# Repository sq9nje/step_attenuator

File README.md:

# Weinschel Step Attenuator Controller

## Links
- [WT32-ETH01](https://github.com/egnor/wt32-eth01)

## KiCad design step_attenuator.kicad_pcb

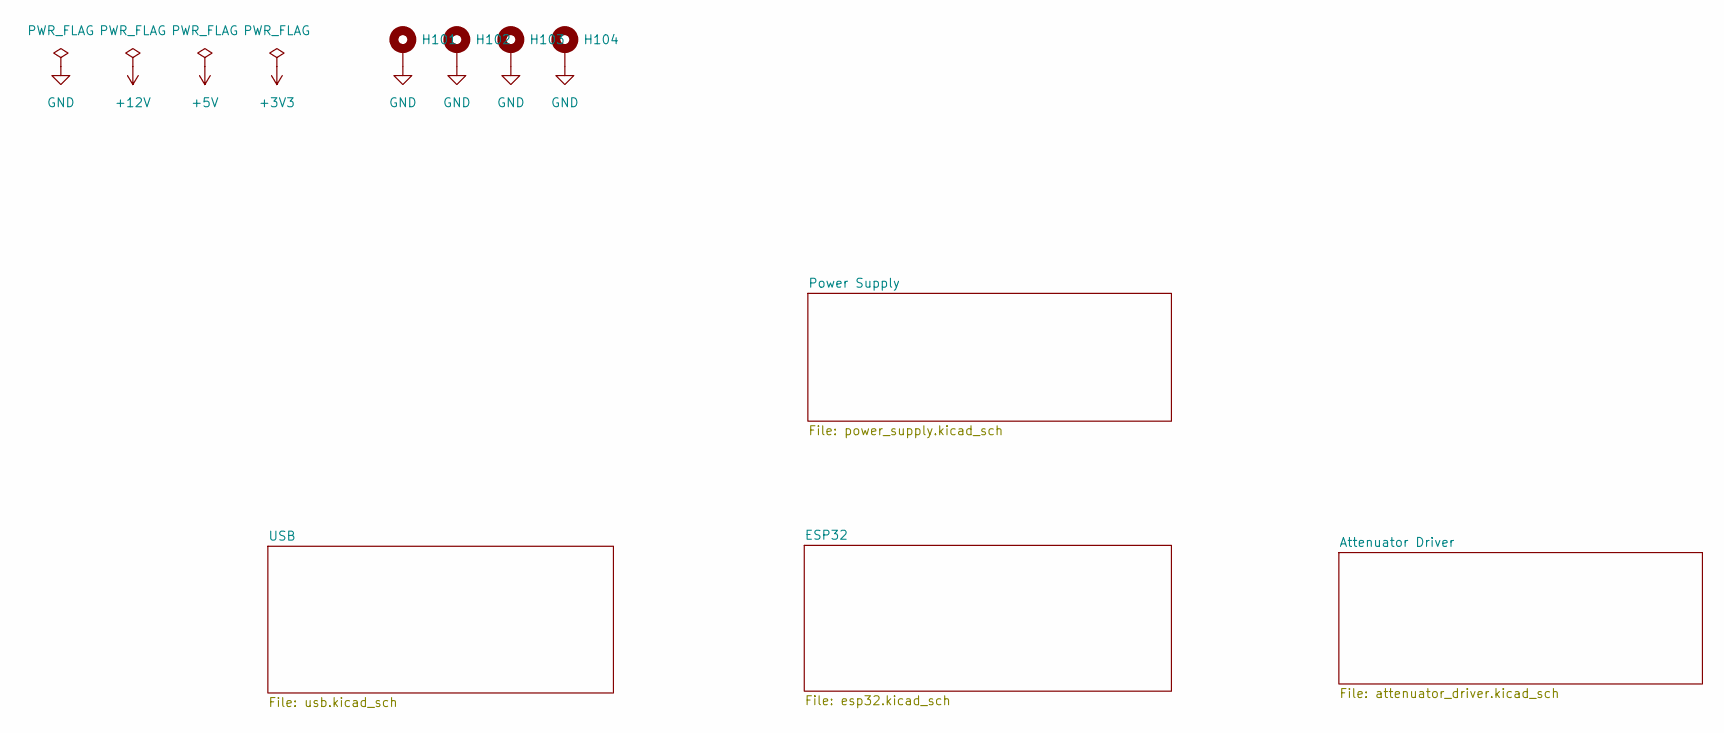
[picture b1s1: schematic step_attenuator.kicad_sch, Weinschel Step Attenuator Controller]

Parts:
H101, H102, H103, H104: MountingHole_Pad; MountingHole_3.2mm_M3_Pad_Via

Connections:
GND: H101.1, H102.1, H103.1, H104.1; also elsewhere on the board

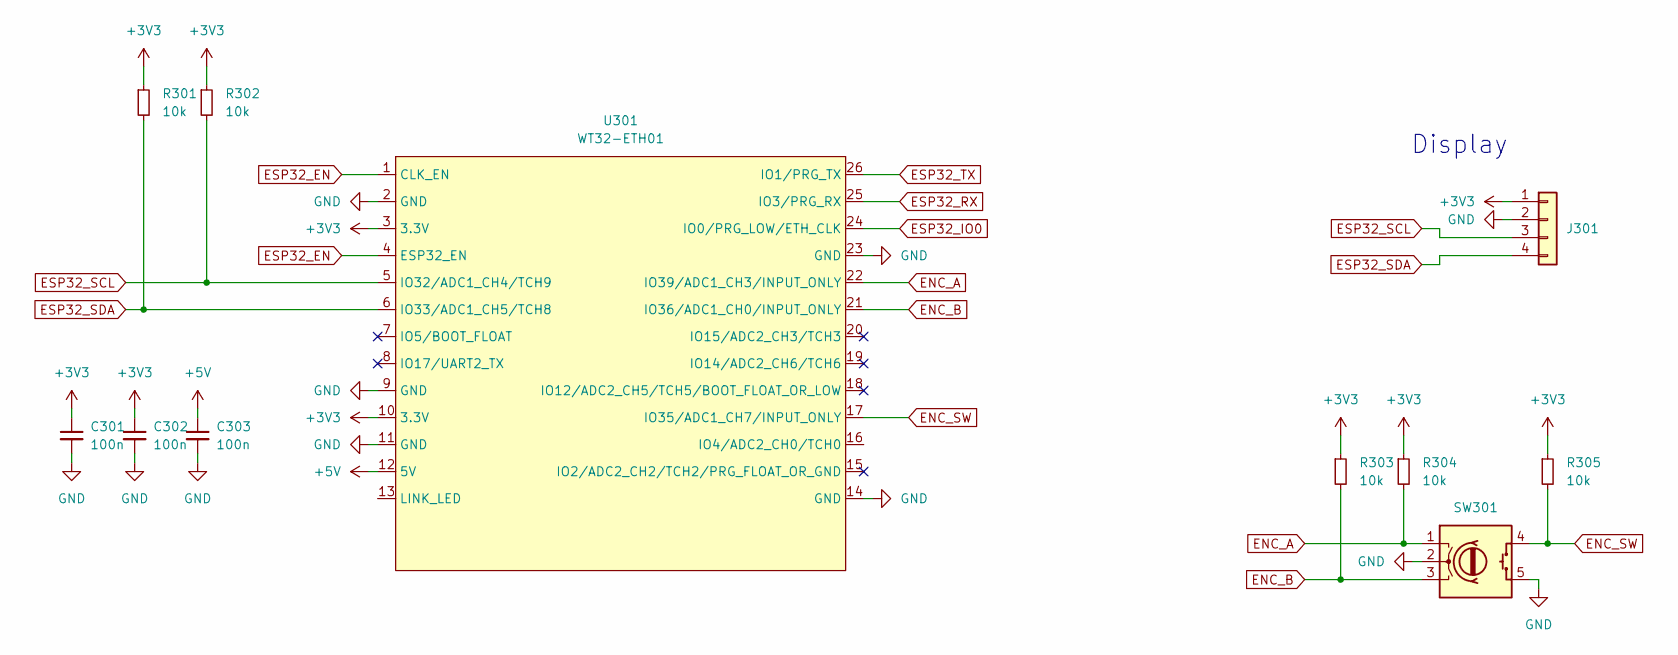
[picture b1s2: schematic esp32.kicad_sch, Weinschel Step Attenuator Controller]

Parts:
C301, C302, C303: 100n; C_0603_1608Metric_Pad1.08x0.95mm_HandSolder
J301: Conn_01x04; JST_XH_B4B-XH-A_1x04_P2.50mm_Vertical
R301, R302, R303, R304, R305: 10k; R_0603_1608Metric_Pad0.98x0.95mm_HandSolder
SW301: RotaryEncoder_Switch; JST_XH_B5B-XH-A_1x05_P2.50mm_Vertical
U301: WT32-ETH01

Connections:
+3V3: C301.1, C302.1, J301.1, R301.1, R302.1, R303.1, R304.1, R305.1, U301.3 (3.3V), U301.10 (3.3V); also elsewhere on the board
+5V: C303.1, U301.12 (5V); also elsewhere on the board
ENC_A: R304.2, SW301.1 (A), U301.22 (IO39/ADC1_CH3/INPUT_ONLY)
ENC_B: R303.2, SW301.3 (B), U301.21 (IO36/ADC1_CH0/INPUT_ONLY)
ENC_SW: R305.2, SW301.4 (S1), U301.17 (IO35/ADC1_CH7/INPUT_ONLY)
ESP32_EN: U301.1 (CLK_EN), U301.4 (ESP32_EN); also elsewhere on the board
ESP32_IO0: U301.24 (IO0/PRG_LOW/ETH_CLK); also elsewhere on the board
ESP32_RX: U301.25 (IO3/PRG_RX); also elsewhere on the board
ESP32_SCL: J301.3, R302.2, U301.5 (IO32/ADC1_CH4/TCH9); also elsewhere on the board
ESP32_SDA: J301.4, R301.2, U301.6 (IO33/ADC1_CH5/TCH8); also elsewhere on the board
ESP32_TX: U301.26 (IO1/PRG_TX); also elsewhere on the board
GND: C301.2, C302.2, C303.2, J301.2, SW301.2 (C), SW301.5 (S2), U301.2 (GND), U301.9 (GND), U301.11 (GND), U301.14 (GND), U301.23 (GND); also elsewhere on the board

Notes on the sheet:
Display

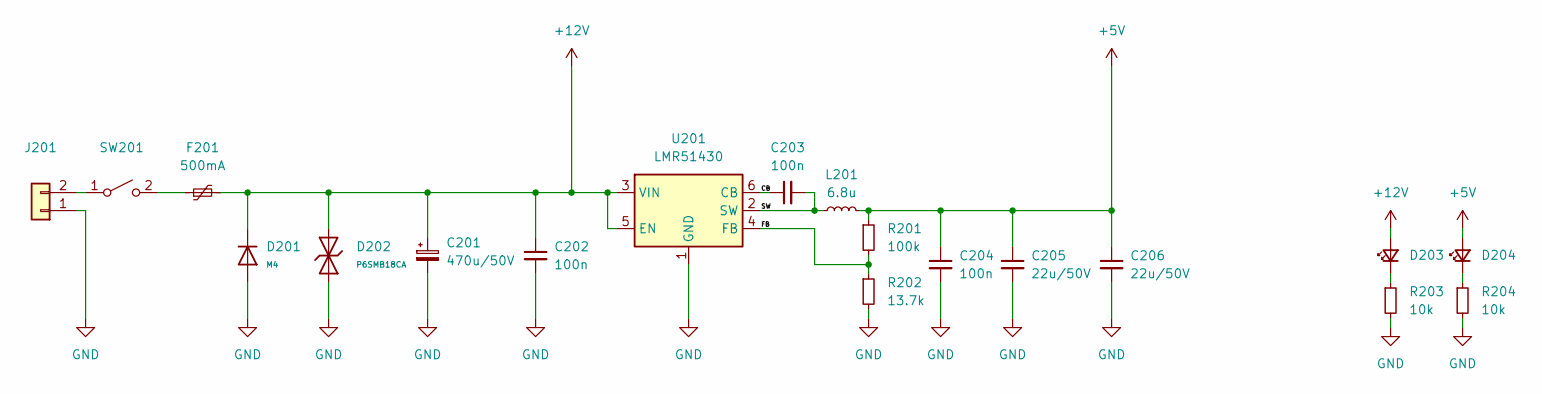
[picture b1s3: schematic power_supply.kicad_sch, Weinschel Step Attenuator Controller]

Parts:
C201: 470u/50V; CP_Radial_D10.0mm_P5.00mm
C202, C203, C204: 100n; C_0603_1608Metric
C205, C206: 22u/50V; C_1206_3216Metric
D201: M4; D_SMA; Forward Voltage (Vf@If) 1V@1A; Reverse Voltage (Vr) 400V; Part M4; LCSC C18199095
D202: P6SMB18CA; D_SMB; Part P6SMB18CA; LCSC C19077599
D203, D204: LED_Small; D_0805_2012Metric_Pad1.15x1.40mm_HandSolder
F201: 500mA; Fuse_1206_3216Metric_Pad1.42x1.75mm_HandSolder
J201: Conn_01x02; AMASS_XT60PW-M_1x02_P7.20mm_Horizontal
L201: 6.8u; L_10.4x10.4_H4.8
R201: 100k; R_0603_1608Metric
R202: 13.7k; R_0603_1608Metric
R203, R204: 10k; R_0603_1608Metric_Pad0.98x0.95mm_HandSolder
SW201: SW_SPST; Molex_KK-254_AE-6410-02A_1x02_P2.54mm_Vertical
U201: LMR51430; SOT-23-6

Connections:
+5V: C204.1, C205.1, C206.1, D204.2 (A), L201.2, R201.1; also elsewhere on the board
+12V: C201.1, C202.1, D201.1, D202.1, D203.2 (A), F201.2, U201.3 (VIN), U201.5 (EN); also elsewhere on the board
/Power Supply/CB: C203.1, U201.6 (CB)
/Power Supply/FB: R201.2, R202.1, U201.4 (FB)
/Power Supply/SW: C203.2, L201.1, U201.2 (SW)
GND: C201.2, C202.2, C204.2, C205.2, C206.2, D201.2, D202.2, J201.1, R202.2, R203.2, R204.2, U201.1 (GND); also elsewhere on the board
unnamed: D203.1 (K), R203.1
unnamed: D204.1 (K), R204.1
unnamed: J201.2, SW201.1 (A)
unnamed: F201.1, SW201.2 (B)

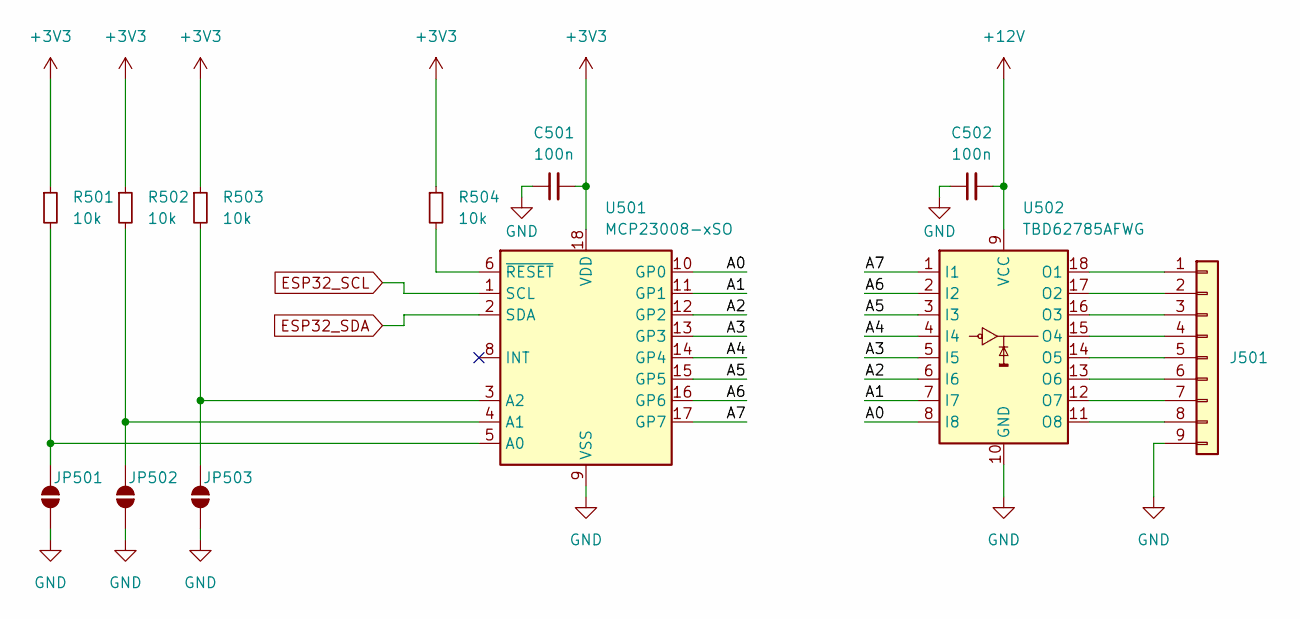
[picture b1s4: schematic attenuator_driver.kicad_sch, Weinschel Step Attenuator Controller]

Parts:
C501, C502: 100n; C_0603_1608Metric_Pad1.08x0.95mm_HandSolder
J501: Conn_01x09; JST_XH_B9B-XH-A_1x09_P2.50mm_Vertical
JP501, JP502, JP503: SolderJumper_2_Open; SolderJumper-2_P1.3mm_Open_RoundedPad1.0x1.5mm
R501, R502, R503, R504: 10k; R_0603_1608Metric_Pad0.98x0.95mm_HandSolder
U501: MCP23008-xSO; SOIC-18W_7.5x11.6mm_P1.27mm
U502: TBD62785AFWG; SOP-18_7.495x11.515mm_P1.27mm

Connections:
+3V3: C501.2, R501.1, R502.1, R503.1, R504.1, U501.18 (VDD); also elsewhere on the board
+12V: C502.2, U502.9 (VCC); also elsewhere on the board
/Attenuator Driver/A0: U501.10 (GP0), U502.8 (I8)
/Attenuator Driver/A1: U501.11 (GP1), U502.7 (I7)
/Attenuator Driver/A2: U501.12 (GP2), U502.6 (I6)
/Attenuator Driver/A3: U501.13 (GP3), U502.5 (I5)
/Attenuator Driver/A4: U501.14 (GP4), U502.4 (I4)
/Attenuator Driver/A5: U501.15 (GP5), U502.3 (I3)
/Attenuator Driver/A6: U501.16 (GP6), U502.2 (I2)
/Attenuator Driver/A7: U501.17 (GP7), U502.1 (I1)
ESP32_SCL: U501.1 (SCL); also elsewhere on the board
ESP32_SDA: U501.2 (SDA); also elsewhere on the board
GND: C501.1, C502.1, J501.9, JP501.1 (A), JP502.1 (A), JP503.1 (A), U501.9 (VSS), U502.10 (GND); also elsewhere on the board
unnamed: J501.1, U502.18 (O1)
unnamed: J501.2, U502.17 (O2)
unnamed: J501.3, U502.16 (O3)
unnamed: J501.4, U502.15 (O4)
unnamed: J501.5, U502.14 (O5)
unnamed: J501.6, U502.13 (O6)
unnamed: J501.7, U502.12 (O7)
unnamed: J501.8, U502.11 (O8)
unnamed: JP501.2 (B), R501.2, U501.5 (A0)
unnamed: JP502.2 (B), R502.2, U501.4 (A1)
unnamed: JP503.2 (B), R503.2, U501.3 (A2)
unnamed: R504.2, U501.6 (~RESET)

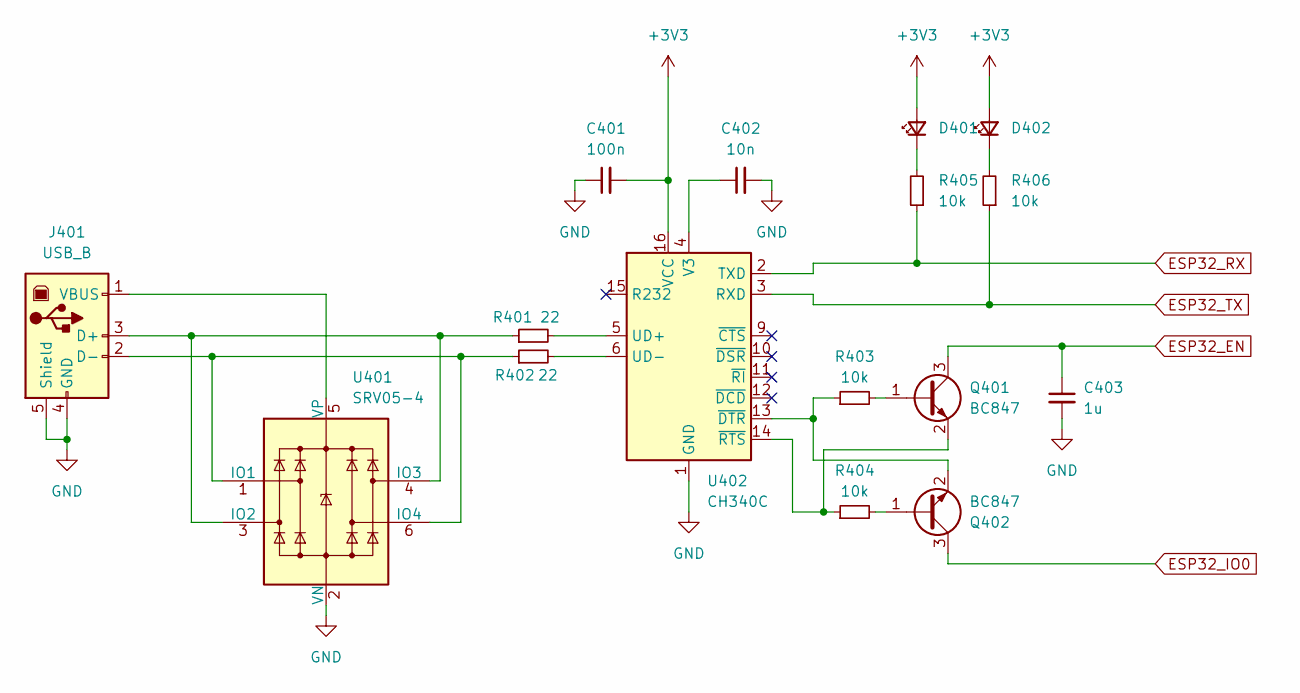
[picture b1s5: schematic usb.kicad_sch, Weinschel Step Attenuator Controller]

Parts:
C401: 100n; C_0603_1608Metric_Pad1.08x0.95mm_HandSolder
C402: 10n; C_0603_1608Metric_Pad1.08x0.95mm_HandSolder
C403: 1u; C_0603_1608Metric_Pad1.08x0.95mm_HandSolder
D401, D402: LED_Small; D_0805_2012Metric_Pad1.15x1.40mm_HandSolder
J401: USB_B; USB_B_Lumberg_2411_02_Horizontal
Q401, Q402: BC847; SOT-23
R401, R402: 22; R_0603_1608Metric_Pad0.98x0.95mm_HandSolder
R403, R404, R405, R406: 10k; R_0603_1608Metric_Pad0.98x0.95mm_HandSolder
U401: SRV05-4; SOT-23-6
U402: CH340C; SOIC-16_3.9x9.9mm_P1.27mm

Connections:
+3V3: C401.2, D401.2 (A), D402.2 (A), U402.16 (VCC); also elsewhere on the board
ESP32_EN: C403.1, Q401.3 (C); also elsewhere on the board
ESP32_IO0: Q402.3 (C); also elsewhere on the board
ESP32_RX: R405.1, U402.2 (TXD); also elsewhere on the board
ESP32_TX: R406.1, U402.3 (RXD); also elsewhere on the board
GND: C401.1, C402.2, C403.2, J401.4 (GND), J401.5 (Shield), U401.2 (VN), U402.1 (GND); also elsewhere on the board
unnamed: D401.1 (K), R405.2
unnamed: D402.1 (K), R406.2
unnamed: J401.3 (D+), R401.1, U401.3 (IO2), U401.4 (IO3)
unnamed: J401.2 (D-), R402.1, U401.1 (IO1), U401.6 (IO4)
unnamed: J401.1 (VBUS), U401.5 (VP)
unnamed: Q401.1 (B), R403.2
unnamed: Q401.2 (E), R404.1, U402.14 (~RTS)
unnamed: Q402.1 (B), R404.2
unnamed: Q402.2 (E), R403.1, U402.13 (~DTR)
unnamed: R401.2, U402.5 (UD+)
unnamed: R402.2, U402.6 (UD-)
unnamed: C402.1, U402.4 (V3)

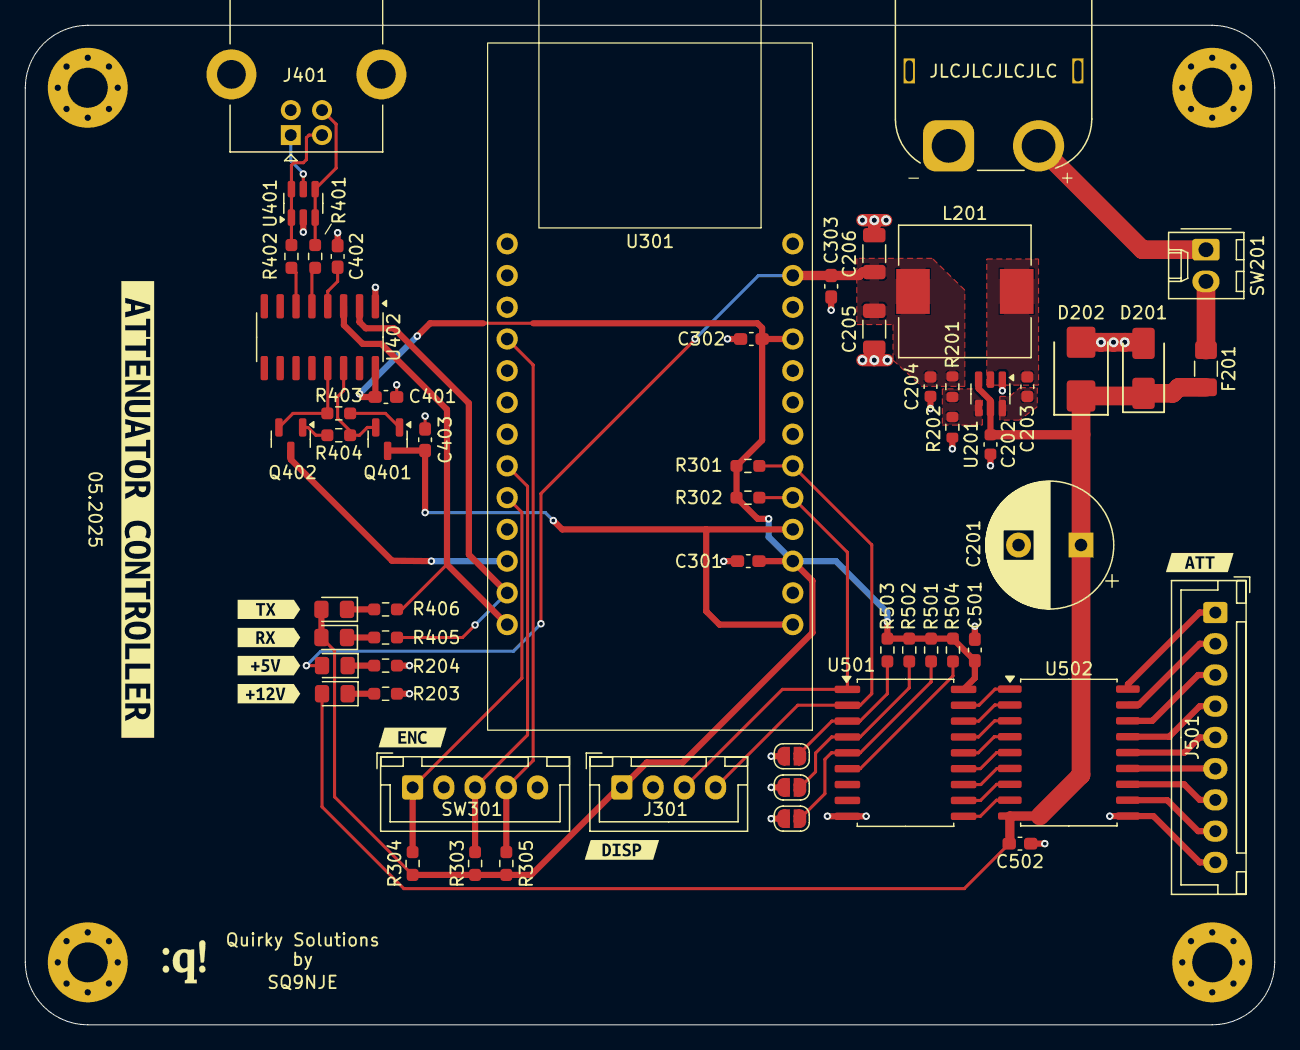
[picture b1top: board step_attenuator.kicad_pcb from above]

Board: 2 copper layers, 100.0 x 80.0 mm, 71 parts (0 on the bottom side), 52 nets.

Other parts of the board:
Ref**: Val**; qs_logo
kibuzzard-68053CB6: G***; kibuzzard-68053CB6
kibuzzard-68053CC3: G***; kibuzzard-68053CC3
kibuzzard-68053CCC: G***; kibuzzard-68053CCC
kibuzzard-68053CD4: G***; kibuzzard-68053CD4
kibuzzard-68053E7E: G***; kibuzzard-68053E7E
kibuzzard-68053E53: G***; kibuzzard-68053E53
kibuzzard-68053EA0: G***; kibuzzard-68053EA0
kibuzzard-68054915: G***; kibuzzard-68054915

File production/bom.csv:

Designator,Footprint,Quantity,Value,LCSC Part #
C201,CP_Radial_D10.0mm_P5.00mm,1,470u/50V,
"C202, C203, C204, C301, C302, C303, C401, C501, C502",0603,9,100n,
"C205, C206",1206,2,22u/50V,
C402,0603,1,10n,
C403,0603,1,1u,
D201,D_SMA,1,M4,C18199095
D202,D_SMB,1,P6SMB18CA,C19077599
"D203, D204, D401, D402",0805,4,LED_Small,
F201,1206,1,500mA,
J201,AMASS_XT60PW-M_1x02_P7.20mm_Horizontal,1,Conn_01x02,
J301,JST_XH_B4B-XH-A_1x04_P2.50mm_Vertical,1,Conn_01x04,
J401,USB_B_Lumberg_2411_02_Horizontal,1,USB_B,
J501,JST_XH_B9B-XH-A_1x09_P2.50mm_Vertical,1,Conn_01x09,
L201,L_10.4x10.4_H4.8,1,6.8u,
"Q401, Q402",SOT-23,2,BC847,
R201,0603,1,100k,
R202,0603,1,13.7k,
"R203, R204, R301, R302, R303, R304, R305, R403, R404, R405, R406, R501, R502, R503, R504",0603,15,10k,
"R401, R402",0603,2,22,
SW201,Molex_KK-254_AE-6410-02A_1x02_P2.54mm_Vertical,1,SW_SPST,
SW301,JST_XH_B5B-XH-A_1x05_P2.50mm_Vertical,1,RotaryEncoder_Switch,
U201,SOT-23-6,1,LMR51430,
U301,WT32-ETH01,1,WT32-ETH01,
U401,SOT-23-6,1,SRV05-4,
U402,SOIC-16_3.9x9.9mm_P1.27mm,1,CH340C,
U501,SOIC-18W_7.5x11.6mm_P1.27mm,1,MCP23008-xSO,
U502,SOP-18_7.495x11.515mm_P1.27mm,1,TBD62785AFWG,

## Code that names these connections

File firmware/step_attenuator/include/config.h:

#ifndef _CONFIG_H_
#define _CONFIG_H_

#define MIN_ATTENUATION 0.0f
#define MAX_ATTENUATION 127.0f
#define ATTENUATION_STEP 1.0f

#define SCL_PIN 32
#define SDA_PIN 33

#define ENC_A_PIN 39
#define ENC_B_PIN 36
#define ENC_SW_PIN 35

#define MCP23008_ADDRESS 0x27

// WiFi Configuration
#define WIFI_MANAGER_AP_NAME "StepAttenuator"
#define WIFI_MANAGER_AP_PASS "configure"
#define SCPI_TCP_PORT 5025
#define TELNET_PORT 23
#define HTTP_PORT 80
#define MAX_TCP_CLIENTS 4

#endif // _CONFIG_H_

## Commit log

2025-05-12 Hardware 05.2025
2025-05-12 .gitignore
2025-05-12 Initial SCPI commands
2025-05-25 web interface
2025-05-25 fw-0.1.0
2025-06-04 FW 0.1.0
